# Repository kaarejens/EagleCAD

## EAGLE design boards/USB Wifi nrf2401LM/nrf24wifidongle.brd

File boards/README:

#EagleCAD->boards

GNU licensed board designs

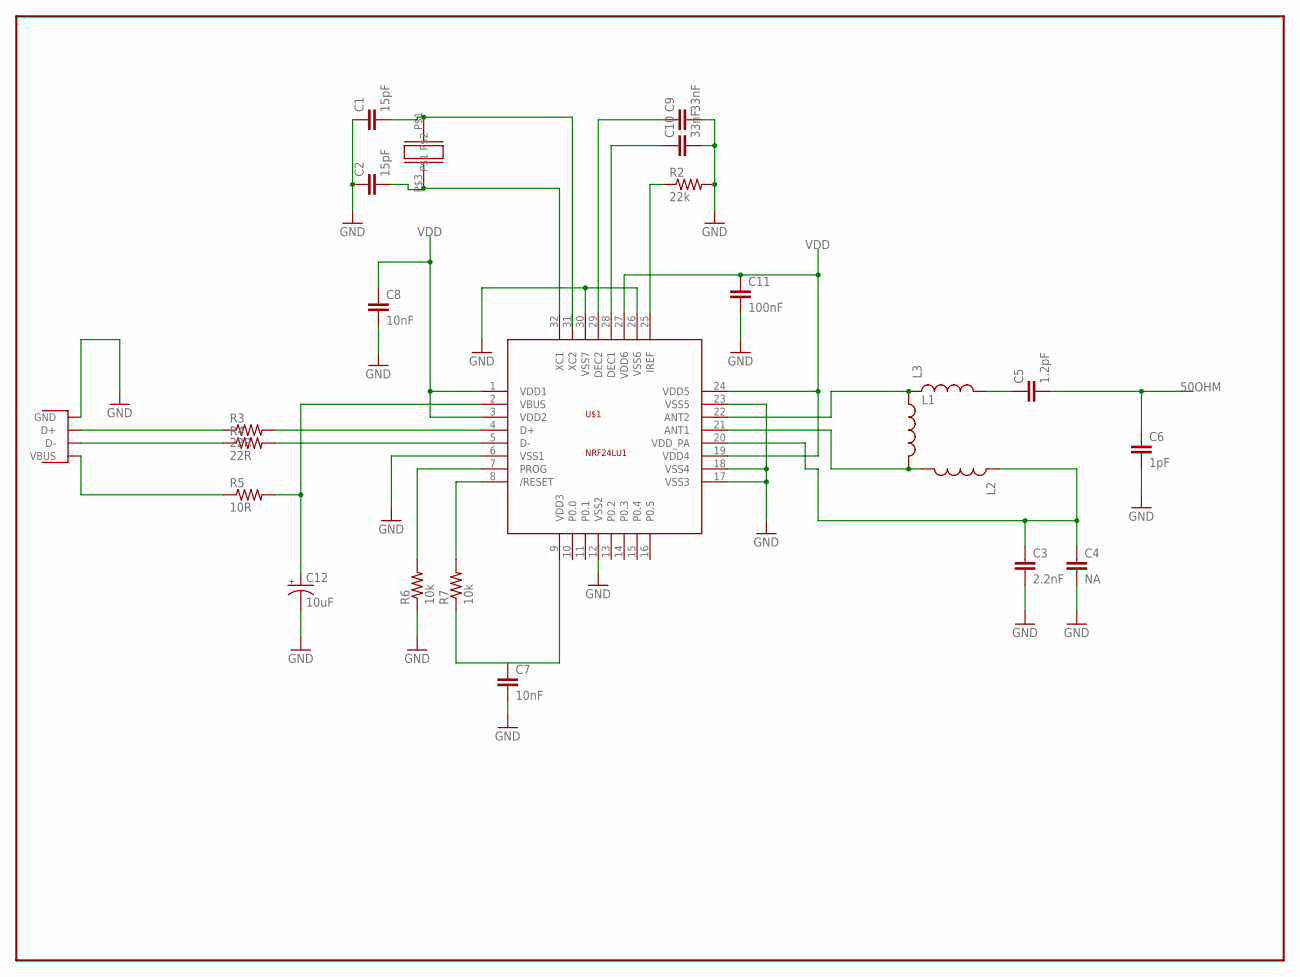
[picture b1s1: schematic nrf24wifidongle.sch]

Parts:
C1, C2: 15pF; C0402
C3: 2.2nF; C0402
C4: NA; C0402
C5: 1.2pF; C0402
C6: 1pF; C0402
C7, C8: 10nF; C0402
C9, C10: 33nF; C0402
C11: 100nF; C0402
C12: 10uF; EIA3216
L1, L2, L3: INDUCTOR0402; C0402
R2: 22k; 0402-RES
R3, R4: 22R; 0402-RES
R5: 10R; 0402-RES
R6, R7: 10k; 0402-RES
U$1: NRF24LU1; QFN-32
U$2: CFPX180
X1: USBPTH; USB-B-PTH

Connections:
50OHM: C5.2, C6.1
GND: C1.1, C2.1, C3.2, C4.2, C6.2, C7.2, C8.2, C9.2, C10.2, C11.2, C12.C (-), R2.2, R6.1, U$1.6 (VSS1), U$1.12 (VSS2), U$1.17 (VSS3), U$1.18 (VSS4), U$1.23 (VSS5), U$1.26 (VSS6), U$1.30 (VSS7), X1.GND
unnamed: R3.2, U$1.4 (D+)
unnamed: R4.2, U$1.5 (D-)
unnamed: R3.1, X1.D+
unnamed: R4.1, X1.D-
unnamed: C1.2, U$2.P$1
unnamed: C2.2, U$1.32 (XC1), U$2.P$3
unnamed: C9.1, U$1.29 (DEC2)
unnamed: R5.1, X1.VBUS
unnamed: C12.A (+), R5.2, U$1.2 (VBUS)
unnamed: R6.2, U$1.7 (PROG)
unnamed: R7.2, U$1.8 (/RESET)
unnamed: R7.1, U$1.9 (VDD3)
unnamed: R2.1, U$1.25 (IREF)
unnamed: C5.1, L3.2
unnamed: C10.1, U$1.28 (DEC1)
unnamed: L1.1, L3.1, U$1.22 (ANT2)
unnamed: C3.1, C4.1, L2.1, U$1.20 (VDD_PA)
unnamed: L1.2, L2.2, U$1.21 (ANT1)
VDD: C8.1, C11.1, U$1.1 (VDD1), U$1.3 (VDD2), U$1.19 (VDD4), U$1.24 (VDD5), U$1.27 (VDD6)

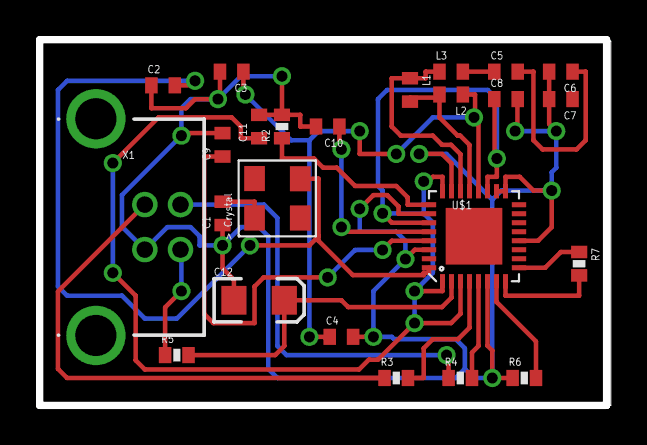
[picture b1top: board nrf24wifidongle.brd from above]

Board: 2 copper layers, 31.7 x 20.3 mm, 24 parts (0 on the bottom side), 21 nets.

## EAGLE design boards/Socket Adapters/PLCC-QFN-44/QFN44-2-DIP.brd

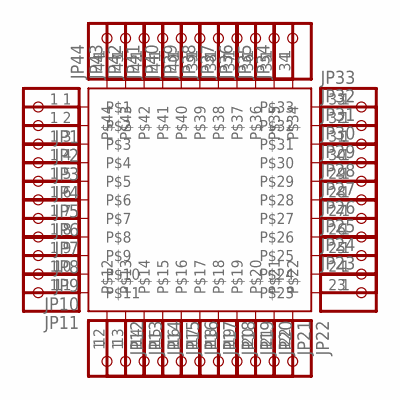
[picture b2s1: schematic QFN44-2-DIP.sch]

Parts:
JP1, JP2, JP3, JP4, JP5, JP6, JP7, JP8, JP9, JP10, JP11, JP12, JP13, JP14, JP15, JP16, JP17, JP18, JP19, JP20, JP21, JP22, JP23, JP24, JP25, JP26, JP27, JP28, JP29, JP30, JP31, JP32, JP33, JP34, JP35, JP36, JP37, JP38, JP39, JP40, JP41, JP42, JP43, JP44: PINHD-1X1; 1X01
U$1: 3M44

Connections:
unnamed: JP1.1, U$1.1
unnamed: JP2.1, U$1.2
unnamed: JP3.1, U$1.3
unnamed: JP4.1, U$1.4
unnamed: JP5.1, U$1.5
unnamed: JP6.1, U$1.6
unnamed: JP7.1, U$1.7
unnamed: JP8.1, U$1.8
unnamed: JP9.1, U$1.9
unnamed: JP10.1, U$1.10
unnamed: JP11.1, U$1.11
unnamed: JP12.1, U$1.12
unnamed: JP13.1, U$1.13
unnamed: JP14.1, U$1.14
unnamed: JP15.1, U$1.15
unnamed: JP16.1, U$1.16
unnamed: JP17.1, U$1.17
unnamed: JP18.1, U$1.18
unnamed: JP19.1, U$1.19
unnamed: JP20.1, U$1.20
unnamed: JP21.1, U$1.21
unnamed: JP22.1, U$1.22
unnamed: JP23.1, U$1.23
unnamed: JP24.1, U$1.24
unnamed: JP25.1, U$1.25
unnamed: JP26.1, U$1.26
unnamed: JP27.1, U$1.27
unnamed: JP28.1, U$1.28
unnamed: JP29.1, U$1.29
unnamed: JP30.1, U$1.30
unnamed: JP31.1, U$1.31
unnamed: JP32.1, U$1.32
unnamed: JP33.1, U$1.33
unnamed: JP34.1, U$1.34
unnamed: JP35.1, U$1.35
unnamed: JP36.1, U$1.36
unnamed: JP37.1, U$1.37
unnamed: JP38.1, U$1.38
unnamed: JP39.1, U$1.39
unnamed: JP40.1, U$1.40
unnamed: JP41.1, U$1.41
unnamed: JP42.1, U$1.42
unnamed: JP43.1, U$1.43
unnamed: JP44.1, U$1.44

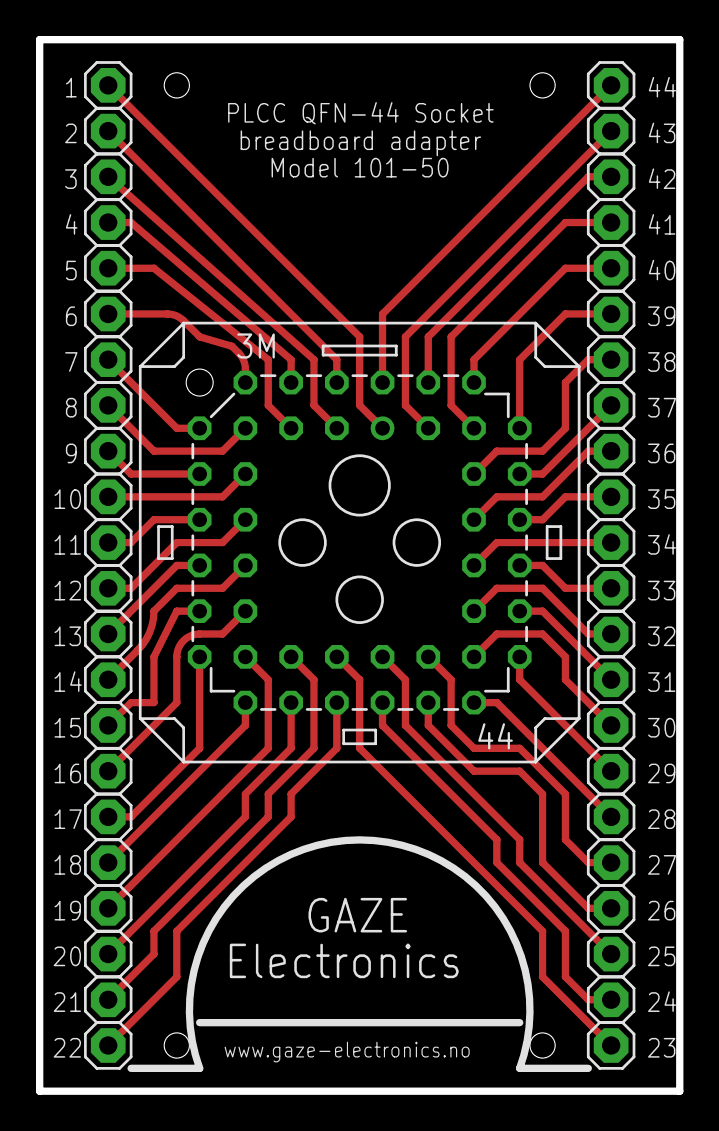
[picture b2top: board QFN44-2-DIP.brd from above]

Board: 2 copper layers, 35.6 x 58.4 mm, 45 parts (0 on the bottom side), 44 nets.

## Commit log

2015-09-19 libraries folder
    A collection of eagle libraries
2015-09-19 README
2015-09-19 QFN-44 to TH socket breakout
2015-09-19 USB nrf24 Wifi Dongle
2015-10-30 libraries
    All sorts of libraries for Eagle CAD
2015-10-30 errors

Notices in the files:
parts and their libraries:
Gaze Electronics - RF: Licensing: Creative Commons ShareAlike 4.0 International - https://creativecommons.org/licenses/by-sa/4.0
